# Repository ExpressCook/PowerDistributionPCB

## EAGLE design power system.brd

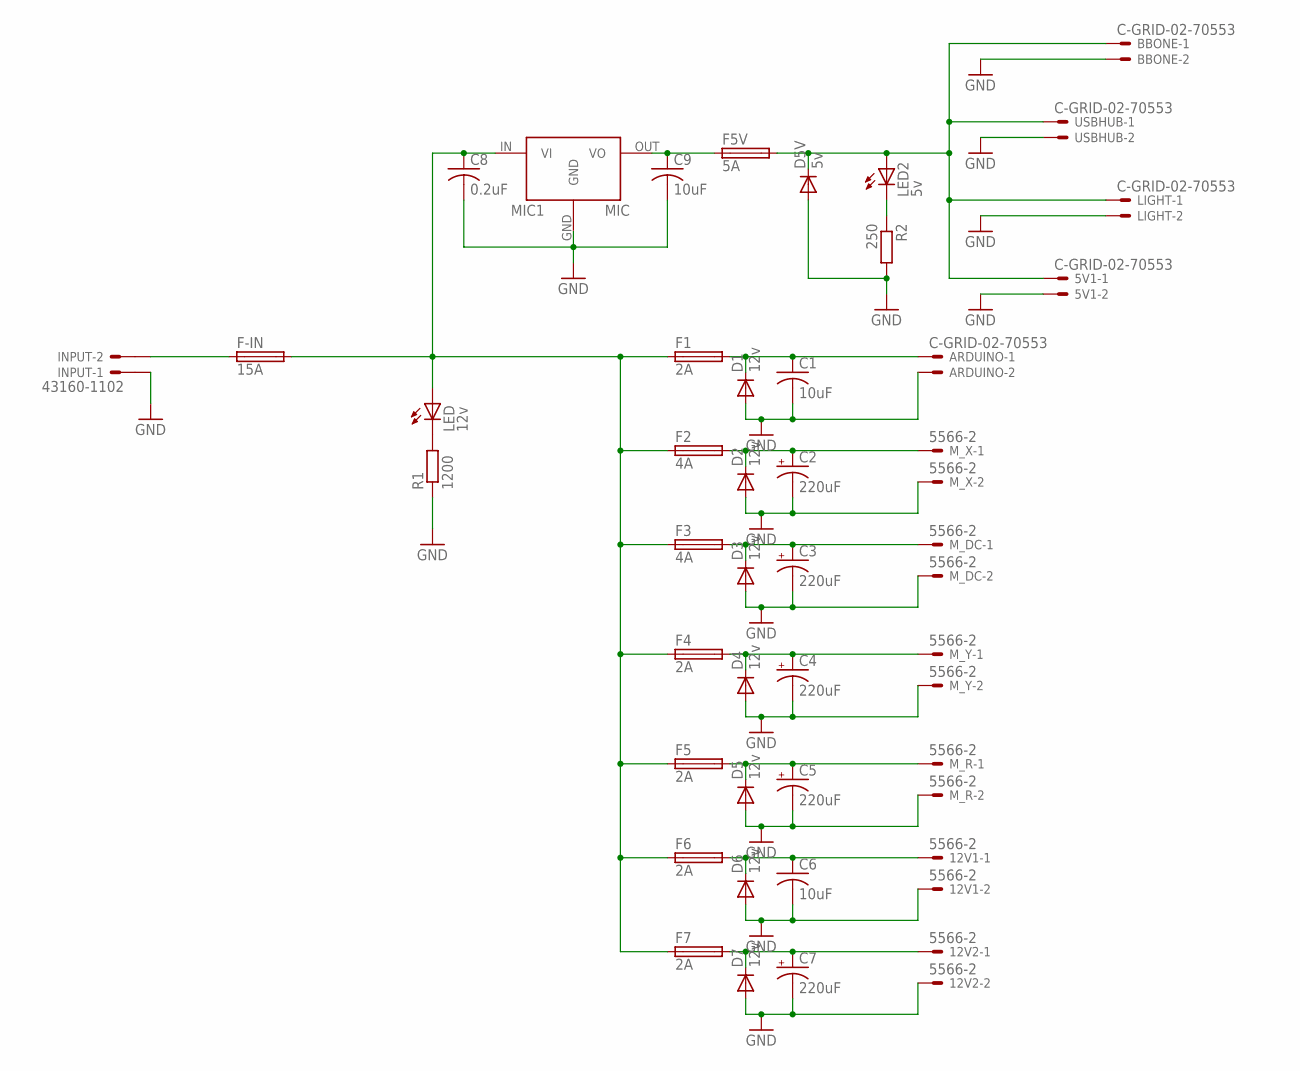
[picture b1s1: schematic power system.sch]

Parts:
5V1: C-GRID-02-70553; 70553-02
12V1, 12V2: 5566-2
ARDUINO: C-GRID-02-70553; 70553-02
BBONE: C-GRID-02-70553; 70553-02
C1, C6, C9: 10uF; C1206
C2, C3, C4, C5, C7: 220uF; NIPPON_F80
C8: 0.2uF; C1206
D1, D2, D3, D4, D5, D6, D7: 12v; DO214AC
D5V: 5v; DO214AC
F1, F4, F5, F6, F7: 2A; TE5
F2, F3: 4A; TE5
F5V: 5A; TE5
F-IN: 15A; FUSE_HOLDER_5X20MM
INPUT: 43160-1102; 43160-XX02
LED: 12v; LED5MM
LED2: 5v; LED5MM
LIGHT: C-GRID-02-70553; 70553-02
MIC1: MIC29300; TO220CS
M_DC: 5566-2
M_R: 5566-2
M_X: 5566-2
M_Y: 5566-2
R1: 1200; R1206
R2: 250; R1206
USBHUB: C-GRID-02-70553; 70553-02

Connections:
GND: 5V1.2, 12V1.2, 12V2.2, ARDUINO.2, BBONE.2, C1.2, C2.-, C3.-, C4.-, C5.-, C6.2, C7.-, C8.2, C9.2, D1.A, D2.A, D3.A, D4.A, D5.A, D5V.A, D6.A, D7.A, INPUT.1@1, LIGHT.2, MIC1.GND, M_DC.2, M_R.2, M_X.2, M_Y.2, R1.1, R2.2, USBHUB.2
unnamed: ARDUINO.1, C1.1, D1.C, F1.2
unnamed: F-IN.1, INPUT.2@1
unnamed: C2.+, D2.C, F2.2, M_X.1
unnamed: 5V1.1, BBONE.1, D5V.C, F5V.2, LED2.A, LIGHT.1, USBHUB.1
unnamed: C3.+, D3.C, F3.2, M_DC.1
unnamed: C9.1, F5V.1, MIC1.OUT (VO)
unnamed: C8.1, F1.1, F2.1, F3.1, F4.1, F5.1, F6.1, F7.1, F-IN.2, LED.A, MIC1.IN (VI)
unnamed: LED2.K (C), R2.1
unnamed: C4.+, D4.C, F4.2, M_Y.1
unnamed: LED.K (C), R1.2
unnamed: C5.+, D5.C, F5.2, M_R.1
unnamed: 12V1.1, C6.1, D6.C, F6.2
unnamed: 12V2.1, C7.+, D7.C, F7.2

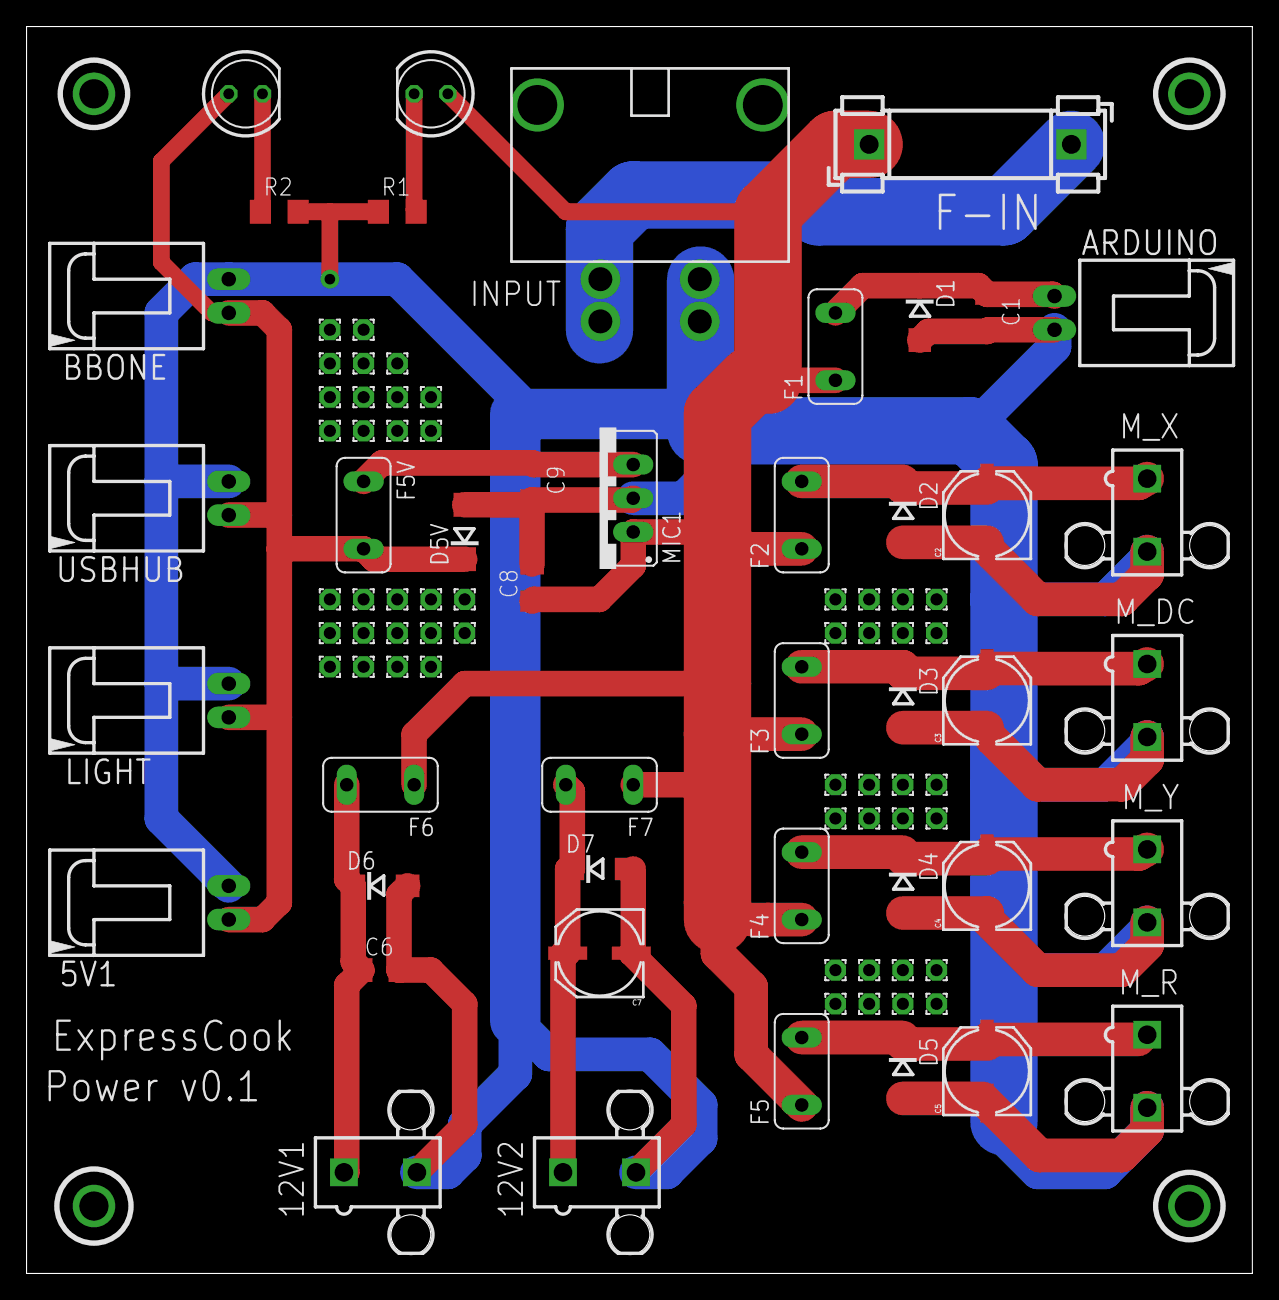
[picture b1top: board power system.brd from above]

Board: 2 copper layers, 92.4 x 94.0 mm, 94 parts (0 on the bottom side), 14 nets.

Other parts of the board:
E$1, E$2, E$3, E$4, E$5, E$6, E$7, E$8, E$9, E$10, E$11, E$12, E$13, E$14, E$15, E$16, E$17, E$18, E$19, E$20, E$21, E$22, E$24, E$25, E$26, E$27, E$30, E$31, E$32, E$33, E$34, E$35, E$36, E$37, E$38, E$39, E$40, E$41, E$42, E$43, E$44, E$45, E$46, E$48, E$49, E$50, E$51, E$52, E$53, E$54, E$55: 1,6/0,9

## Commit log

2014-10-31 init pcb
2014-10-31 add heat sink
2014-11-01 1. increase the wire width 2. merge the two brd file 3. change the fuse value and connector order 4. approve the DRC error
2014-11-01 clear the file
2014-11-01 increas track to 20
2014-11-03 1. add the Gerber files1. add the Gerber files1. add the Gerber files1. add the Gerber files1. add the Gerber files1. add the Gerber files1. add the Gerber files1. add the Gerber files1. add the Gerb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
2014-11-06 BOM change

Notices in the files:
parts and their libraries:
SparkFun-Capacitors: Licensing: Creative Commons ShareAlike 4.0 International - https://creativecommons.org/licenses/by-sa/4.0
